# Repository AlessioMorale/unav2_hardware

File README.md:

View this project on [CADLAB.io](https://cadlab.io/project/25058). 

# unav2_hardware
Initial test hardware for the future STM32F4 based uNav motor controller

## baseboard
An initial, unfinished and untested attempt to design a modular design.

## integrated_board
This is the first iteration of the testing hardware. It is being built but is not tested yet.
[more information](integrated_board/README.md)

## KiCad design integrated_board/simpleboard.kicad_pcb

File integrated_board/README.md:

# Integrated Board
This is the first iteration of test hardware for unav2. The board includes a STM32F405 and two DRV8871 drivers.
It supports motor current feedback using two INA186 and global battery current/voltage monitor using an INA219.
Additionally there is an LM75 temperature monitor ic and a fan output.

Link to [Interactive BOM](https://htmlpreview.github.io/?https://raw.githubusercontent.com/AlessioMorale/unav2_hardware/master/integrated_board/bom/ibom.html) (built with the awesome [InteractiveHtmlBom plugin](https://github.com/openscopeproject/InteractiveHtmlBom) )

Note: Encoder, serial and fan connectors are actually JST SH series, not exactly the type shown.

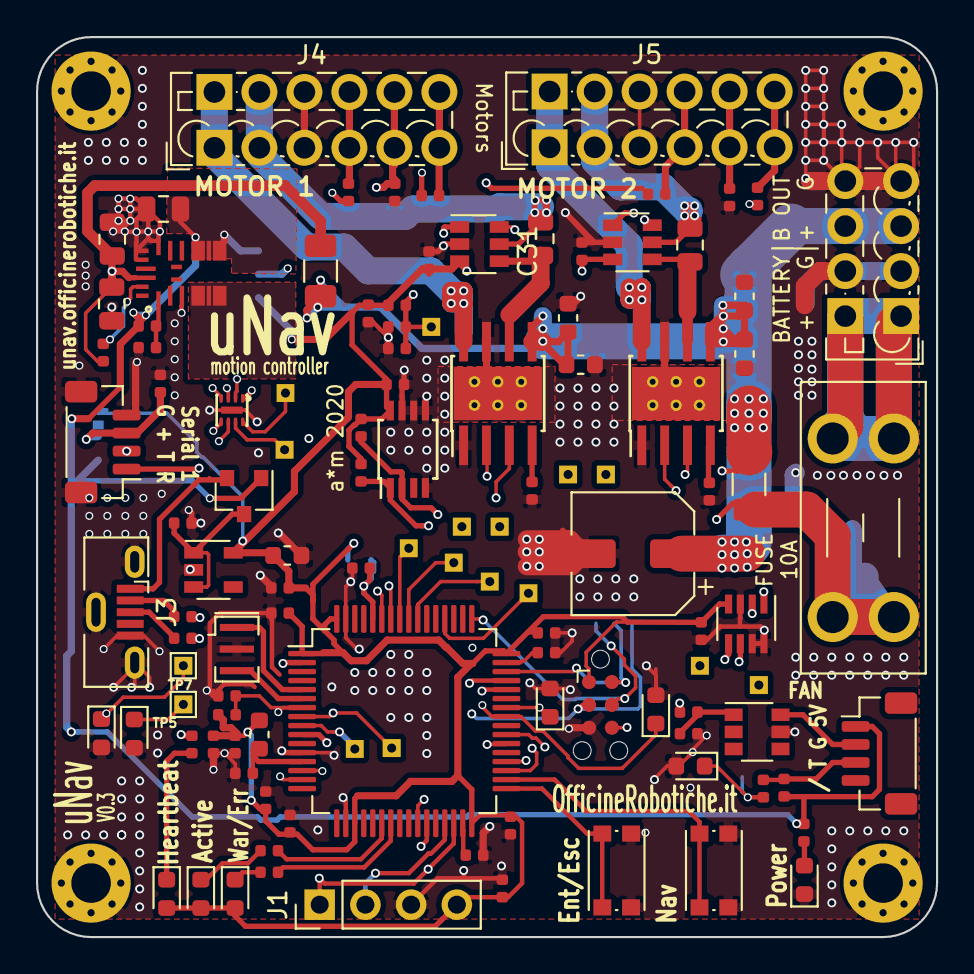
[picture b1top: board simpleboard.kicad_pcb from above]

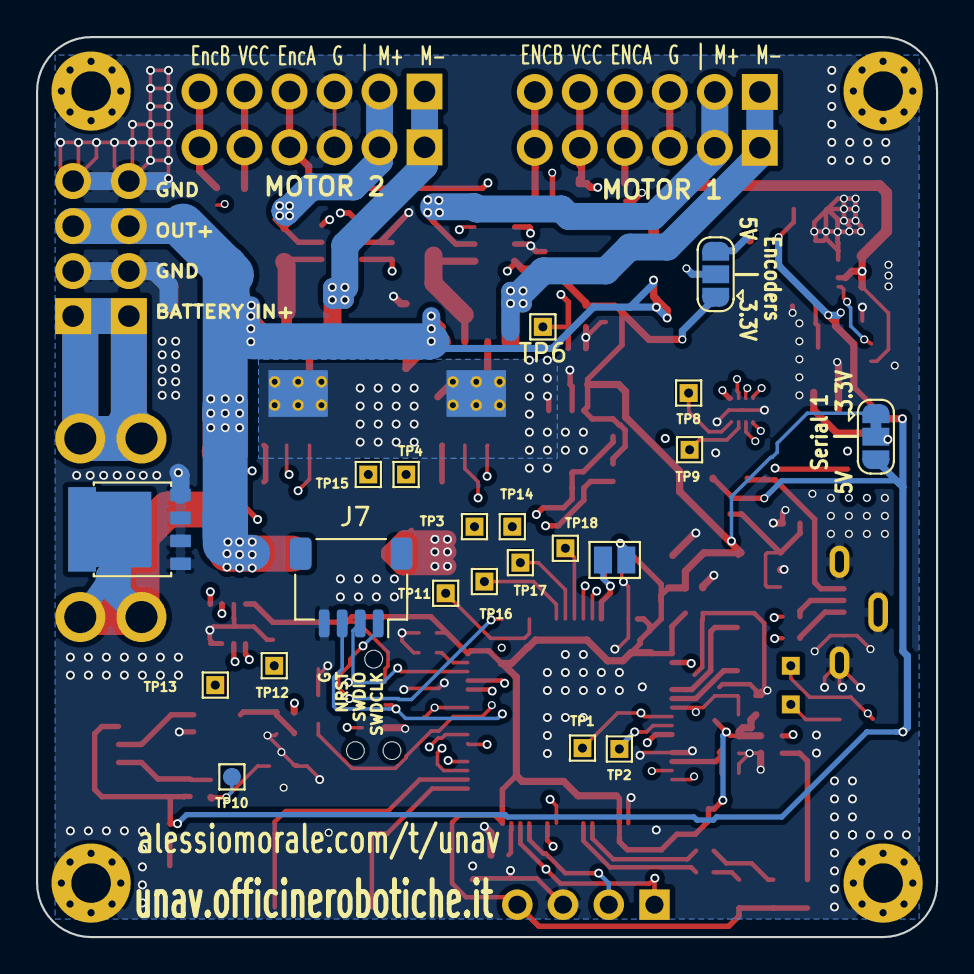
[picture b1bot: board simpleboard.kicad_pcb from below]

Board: 4 copper layers, 50.0 x 50.0 mm, 122 parts (21 on the bottom side), 76 nets.

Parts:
C1: 47uF; CP_Elec_6.3x5.8
C2, C5, C6, C7: 1uF 25V; C_0603_1608Metric
C3, C8, C9, C13, C14, C15, C16, C19, C21, C22, C23, C24, C26, C28, C29, C31, C32: 100nF 16V; C_0402_1005Metric
C4, C11, C12, C25, C27: 1uF 10V; C_0402_1005Metric
C10: 10n; C_0402_1005Metric
C17: 22uF 25V; C_0805_2012Metric
C18: 4.7uf 25V; C_0805_2012Metric
C20: 22uf 6.3V; C_0805_2012Metric
C30: 1uF 6.3V; C_0603_1608Metric
D1: Blue; LED_0603_1608Metric
D2: Yellow; LED_0603_1608Metric
D3: Red; LED_0603_1608Metric
D4: BAT54C; SOT-23
D5: green; LED_0603_1608Metric
D6: STPS3045DJF; LFPAK56
D7, D8, D9, D10: 3.3V; D_0603_1608Metric
D11: D_Zener; D_0603_1608Metric
F1: Fuse_Small; Fuseholder_Blade_Mini_Keystone_3568
F2: Polyfuse_Small; Fuse_1206_3216Metric
H1, H2, H3, H4: MountingHole; MountingHole_2.2mm_M2_Pad_Via
IC1: MPM36xx; QFN-20-MPS-3x5x1.6mm
IC2: IP4251; HUSON8
J1: OLED; PinHeader_1x04_P2.54mm_Vertical
J2: SERIAL1; JST_SH_BM04B-SRSS-TB_1x04-1MP_P1.00mm_Vertical
J3: USB_B_Micro; USB_Micro-B_Molex-105133-0001
J4: Motor1; TerminalBlock_Phoenix_PTSM-0,5-6-2.5-V-THR_1x06_P2.50mm_Ver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
J5: Motor2; TerminalBlock_Phoenix_PTSM-0,5-6-2.5-V-THR_1x06_P2.50mm_Ver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
J6: Battery; TerminalBlock_Phoenix_PTSM-0,5-4-2.5-V-THR_1x04_P2.50mm_Ver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
J7: SWD2; JST_SH_SM04B-SRSS-TB_1x04-1MP_P1.00mm_Horizontal
J8: FAN; JST_SH_BM04B-SRSS-TB_1x04-1MP_P1.00mm_Vertical
JP1: BOOT; SolderJumper-2_P1.3mm_Open_Pad1.0x1.5mm
JP2: S1_VSEL; SolderJumper-3_P1.3mm_Bridged12_RoundedPad1.0x1.5mm
JP3: Jumper_3_Bridged12; SolderJumper-3_P1.3mm_Open_RoundedPad1.0x1.5mm
L1: bead; L_0603_1608Metric
P1: SWD_TC; Tag-Connect_TC2030-IDC-NL_2x03_P1.27mm_Vertical
Q1: FDC6401N; SuperSOT-6
R1, R2, R11, R17, R18, R19, R20, R21, R28: 1k; R_0402_1005Metric
R3, R4: 15k; R_0402_1005Metric
R5, R6: 0.003; R_0805_2012Metric
R7, R8: 47k; R_0402_1005Metric
R9: 220; R_0402_1005Metric
R10: 10k; R_0402_1005Metric
R12: 0.001; R_1206_3216Metric
R13, R22, R23, R24: 330; R_0402_1005Metric
R14, R25: 4.7k; R_0402_1005Metric
R15: 100K; R_0402_1005Metric
R16: 19.1K; R_0402_1005Metric
R26, R27: 22; R_0402_1005Metric
SW1, SW2: KEY_UP; SW_Push_1P1T_NO_CK_KMR2
TP1, TP2, TP3, TP4, TP5, TP6, TP7, TP8, TP9, TP10, TP11, TP12, TP13, TP14, TP15, TP16, TP17, TP18: TestPoint; TestPoint_THTPad_1.0x1.0mm_Drill0.5mm
U1, U6: DRV8871DDA; Texas_HTSOP-8-1EP_3.9x4.9mm_P1.27mm_EP2.95x4.9mm_Mask2.4x3.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
U2: INA219AxDCN; SOT-23-8
U3: LM75B; TSSOP-8_3x3mm_P0.65mm
U4: AP2112K-3.3; SOT-23-5
U5: STM32F405RGTx; LQFP-64_10x10mm_P0.5mm
U7, U8: INA186; SOT-23-6
Y1: 8MHz; Resonator_SMD_muRata_CSTxExxV-3Pin_3.0x1.1mm

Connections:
+3V3: C8.2, C9.2, C13.2, C14.2, C15.1, C16.1, C21.2, C22.2, C23.2, C24.2, C25.2, C27.1, C28.2, C30.1, C32.2, D1.2, D2.2, D3.2, J1.4, JP1.1, JP2.1, JP3.1, L1.1, P1.1, R1.1, R7.1, R14.2, R25.2, U2.4, U3.8, U4.5, U5.1, U5.19, U5.32, U5.48, U5.64, U7.3, U8.3
+5V: C20.1, D4.1, IC1.7, IC1.8, IC1.9, J8.1, JP2.3, JP3.3, R10.2, R15.2, R17.2
/5V_USB: D4.2, J3.1
/ADC_MOT1_CUR: TP1.1, U5.8, U7.6
/ADC_MOT2_CUR: TP2.1, U5.9, U8.6
/ADC_VREF: C4.1, R1.2, R2.1, TP6.1, U5.10, U7.1, U8.1
/BATTERY+: F1.1, J6.1
/BOOT0: JP1.2, R8.1, U5.60
/I2C_SCL: J1.2, R25.1, TP12.1, U2.5, U3.2, U5.29
/I2C_SDA: J1.1, R14.1, TP13.1, U2.6, U3.1, U5.30
/I_KEY0: SW1.1, U5.33
/I_KEY1: SW2.1, U5.34
/NRST: C10.1, J7.3, P1.3, R7.2, U5.7
/O_LED1: R22.1, U5.2
/O_LED2: R23.1, U5.22
/O_LED3: R24.1, U5.23
/O_SPI_CS1: TP11.1, U5.52
/SER1_RX: J2.1, U5.59
/SER1_TX: J2.2, U5.58
/SPI1_MISO: TP17.1, U5.56
/SPI1_MOSI: TP18.1, U5.57
/SPI1_SCK: P1.6, TP16.1, U5.55
/SWCK: J7.1, P1.4, U5.49
/SWDIO: J7.2, P1.2, U5.46
/Sheet5E8E545F/ENC1_A: J4.4, R18.1
/Sheet5E8E545F/ENC1_B: J4.6, R20.1
/Sheet5E8E545F/ENC2_A: J5.4, R19.1
/Sheet5E8E545F/ENC2_B: J5.6, R21.1
/Sheet5E8E545F/ENC_Power: C3.2, C31.1, J4.5, J5.5, JP3.2
/Sheet5E94E0E4/MOT1_A: J4.2, R5.1, U7.5
/Sheet5E94E0E4/MOT1_B: J4.1, U1.8
/Sheet5E94E0E4/MOT2_A: J5.2, R6.1, U8.5
/Sheet5E94E0E4/MOT2_B: J5.1, U6.8
/Sheet5E8941DD/FAN_GND: J8.2, Q1.6
/Sheet5E8941DD/FAN_TACH: J8.3, R10.1, R28.1
/TIM_ENC1_A: D10.1, IC2.1, TP8.1, U5.41
/TIM_ENC1_B: D9.1, IC2.2, TP9.1, U5.42
/TIM_ENC2_A: D8.1, IC2.3, TP7.1, U5.14
/TIM_ENC2_B: D7.1, IC2.4, TP5.1, U5.15
/TIM_FAN_INDEX: D11.1, R28.2, TP10.1, U5.27
/TIM_FAN_PWM: R9.2, U5.26
/TIM_MOT1_A: TP3.1, U1.3, U5.38
/TIM_MOT1_B: TP14.1, U1.2, U5.35
/TIM_MOT2_A: TP4.1, U5.39, U6.3
/TIM_MOT2_B: TP15.1, U5.36, U6.2
/USB_OTG_FS_DM: R27.1, U5.44
/USB_OTG_FS_DP: R26.1, U5.45
/VDDA: C26.1, L1.2, U5.13
/V_BATT_INT: C17.1, C18.1, F2.1, IC1.16, R13.1
GND: C1.2, C2.2, C3.1, C4.2, C5.2, C6.2, C7.2, C8.1, C9.1, C10.2, C11.2, C12.2, C13.1, C14.1, C15.2, C16.2, C17.2, C18.2, C19.2, C20.2, C21.1, C22.1, C23.1, C24.1, C25.1, C26.2, C27.2, C28.1, C29.2, C30.2, C31.2, C32.1, D5.1, D6.1, D6.2, D6.3, D6.4, D7.2, D8.2, D9.2, D10.2, D11.2, H1.1, H2.1, H3.1, H4.1, IC1.3, IC1.12, IC1.13, IC1.14, IC2.9, J1.3, J2.4, J2.MP, J3.5, J3.6, J4.3, J5.3, J6.2, J6.4, J7.4, P1.5, Q1.5, R2.2, R3.2, R4.2, R8.2, R11.1, R16.1, SW1.2, SW2.2, U1.1, U1.7, U1.9, U2.3, U2.7, U2.8, U3.4, U3.5, U3.6, U3.7, U4.2, U5.12, U5.18, U5.63, U6.1, U6.7, U6.9, U7.2, U8.2, Y1.2
unnamed: C11.1, U5.31
unnamed: C12.1, U5.47
unnamed: C19.1, D4.3, U4.1, U4.3
unnamed: C29.1, J2.3, JP2.2
unnamed: D1.1, R22.2
unnamed: D2.1, R23.2
unnamed: D3.1, R24.2
unnamed: D5.2, R17.1
unnamed: D6.5, F1.2, R12.2, U2.1
unnamed: IC1.1, R15.1, R16.2
unnamed: IC1.4, IC1.5, IC1.6
unnamed: IC1.17, R13.2
unnamed: IC2.5, R21.2
unnamed: IC2.6, R19.2
unnamed: IC2.7, R20.2
unnamed: IC2.8, R18.2
unnamed: J3.2, R27.2
unnamed: J3.3, R26.2
unnamed: Q1.1, R9.1, R11.2
unnamed: R3.1, U1.4
unnamed: R4.1, U6.4
unnamed: R5.2, U1.6, U7.4
unnamed: R6.2, U6.6, U8.4
unnamed: U5.5, Y1.1
unnamed: U5.6, Y1.3
VBATT: C1.1, C2.1, C5.1, C6.1, C7.1, F2.2, J6.3, R12.1, U1.5, U2.2, U6.5

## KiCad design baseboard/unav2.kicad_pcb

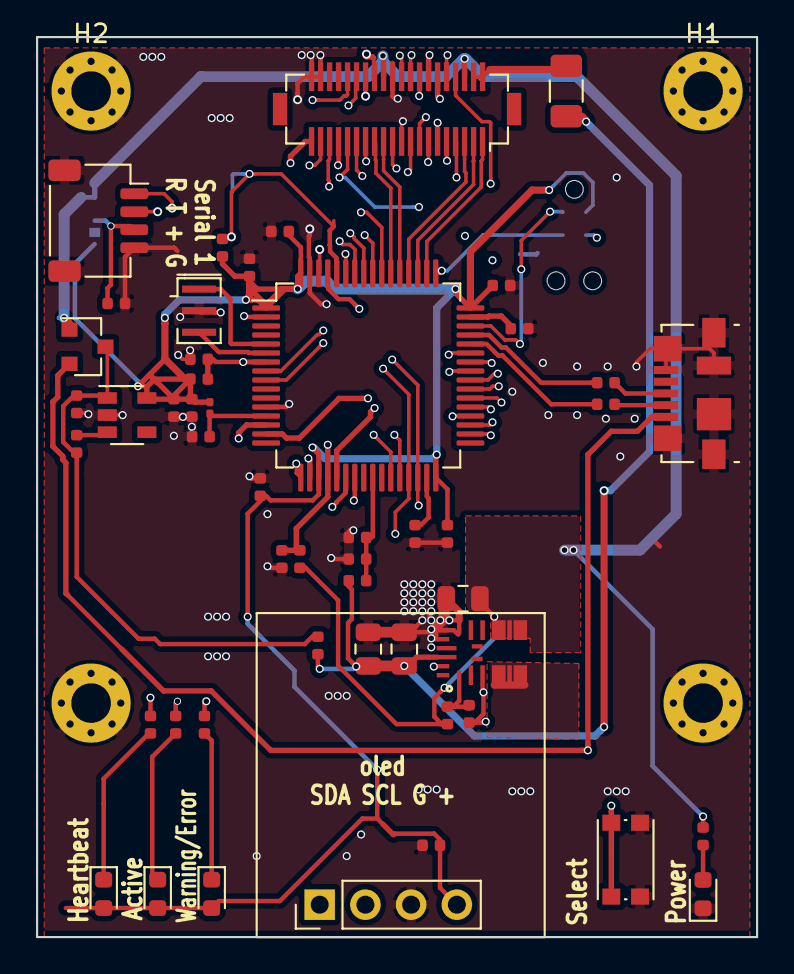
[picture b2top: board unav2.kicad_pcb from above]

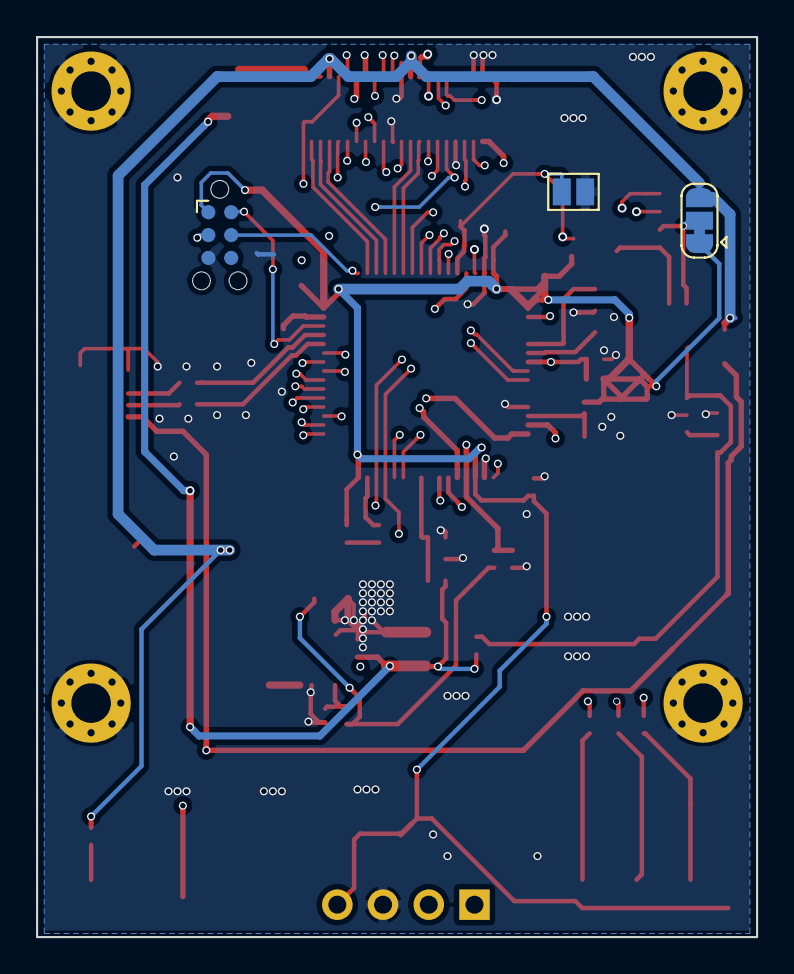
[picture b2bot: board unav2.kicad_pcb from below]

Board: 4 copper layers, 40.0 x 50.0 mm, 57 parts (3 on the bottom side), 65 nets.

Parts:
C3, C7, C13: 1uF; C_0402_1005Metric
C4, C5, C8, C9, C10, C11, C12, C14, C16, C18: 100nF; C_0402_1005Metric
C6, C22: C; C_0402_1005Metric
C15, C19: 4.7uf; C_0805_2012Metric
C17: 22uf; C_0805_2012Metric
C21: 10n; C_0402_1005Metric
D1: White; LED_0603_1608Metric
D2: BAT54C; SOT-23
D3: Blue; LED_0603_1608Metric
D4: Yellow; LED_0603_1608Metric
D5: Red; LED_0603_1608Metric
F1: Polyfuse_Small; Fuse_1206_3216Metric
H1, H2, H3, H4: MountingHole; MountingHole_2.2mm_M2_Pad_Via
IC1: MPM36xx; QFN-20-MPS-3x5x1.6mm
J1: Conn_02x20_Top_Bottom; Hirose_DF12_DF12B-40DS-0.5V(86)
J4: SERIAL1; JST_SH_SM04B-SRSS-TB_1x04-1MP_P1.00mm_Horizontal
J5: OLED; PinHeader_1x04_P2.54mm_Vertical
J6: USB_B_Micro; USB_Micro-B_Molex_47346-0001
JP1: BOOT; SolderJumper-2_P1.3mm_Open_Pad1.0x1.5mm
JP3: S1_VSEL; SolderJumper-3_P1.3mm_Bridged12_RoundedPad1.0x1.5mm
L1: L_Small; L_0201_0603Metric
P1: SWD_TC; Tag-Connect_TC2030-IDC-NL_2x03_P1.27mm_Vertical
R1: 49k; R_0402_1005Metric
R2, R17, R18, R19: 330; R_0402_1005Metric
R3: 10k; R_0402_1005Metric
R4, R5: 10K; R_0402_1005Metric
R6: 22K; R_0402_1005Metric
R7, R14: 47k; R_0402_1005Metric
R10: 22; R_0402_1005Metric
R15, R16: 1k; R_0402_1005Metric
SW1: KEY_UP; SW_Push_1P1T_NO_CK_KMR2
U1: STM32F405RGTx; LQFP-64_10x10mm_P0.5mm
U2: AP2121AK-3.3; SOT-23-5
Y1: 8MHz; Resonator_SMD_muRata_CSTxExxV-3Pin_3.0x1.1mm
e: 22; R_0402_1005Metric

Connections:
+3V3: C4.2, C6.2, C8.2, C9.2, C10.2, C11.2, C12.2, C13.2, D3.2, D4.2, D5.2, J5.4, JP3.1, L1.1, P1.1, R7.1, R14.1, U1.1, U1.19, U1.32, U1.48, U1.64, U2.5
+5V: C17.1, D2.1, IC1.7, IC1.8, IC1.9, J1.23, J1.32, JP3.3, R4.2, R6.2, R16.2
/5V_USB: D2.2, J6.1
/ADC_BATT_VOL: C5.1, R1.1, R15.2, U1.25
/ADC_MOT1_CUR: J1.18, U1.8
/ADC_MOT2_CUR: J1.19, U1.9
/BOOT0: JP1.2, R7.2, U1.60
/I2C_SCL: J1.15, J5.2, U1.29
/I2C_SDA: J1.14, J5.1, U1.30
/I_FAN_INDEX: J1.29, U1.28
/I_FAULT: C18.1, J1.20, R6.1, U1.20
/I_KEY_UP: SW1.1, U1.14
/I_MOT_FAULT: J1.11, U1.34
/NRST: C21.1, P1.3, R14.2, U1.7
/O_LED1: R17.1, U1.2
/O_LED2: R18.1, U1.22
/O_LED3: R19.1, U1.23
/O_MOT_ENABLE: J1.7, U1.37
/O_PWR_MOT_EN: J1.16, U1.43
/O_PWR_SBC_EN: J1.4, U1.40
/O_REG_EN: IC1.17, U1.61
/O_SPI_CS1: J1.3, U1.52
/O_SPI_CS2: J1.2, U1.51
/PA15: J1.1, U1.50
/SER1_RX: J4.1, U1.59
/SER1_TX: J4.2, U1.58
/SER2_RX: J1.13, U1.54
/SER2_TX: J1.12, U1.53
/SPARE_1: J1.33, U1.17
/SPI1_MISO: J1.35, U1.56
/SPI1_MOSI: J1.36, U1.57
/SPI1_SCK: J1.34, U1.55
/SWCK: P1.4, U1.49
/SWDIO: P1.2, U1.46
/TIM_AUX2_PWM: J1.28, U1.62
/TIM_ENC1_A: J1.24, U1.41
/TIM_ENC1_B: J1.25, U1.42
/TIM_ENC2_A: J1.26, U1.21
/TIM_ENC2_B: J1.27, U1.15
/TIM_FAN_PWM: J1.30, U1.27
/TIM_MOT1_A: J1.6, U1.38
/TIM_MOT1_B: J1.9, U1.35
/TIM_MOT2_A: J1.5, U1.39
/TIM_MOT2_B: J1.8, U1.36
/USB_OTG_FS_DM: R10.1, U1.44
/USB_OTG_FS_DP: U1.45, e.1
/V_BATT: C15.1, C19.1, F1.1, IC1.16, R1.2, R2.2
GND: C3.2, C4.1, C5.2, C6.1, C7.2, C8.1, C9.1, C10.1, C11.1, C12.1, C13.1, C14.2, C15.2, C16.2, C17.2, C18.2, C19.2, C21.2, C22.2, D1.1, H1.1, H2.1, H3.1, H4.1, IC1.3, IC1.12, IC1.13, IC1.14, J1.10, J1.17, J1.31, J1.39, J1.40, J4.4, J4.MP, J5.3, J6.5, J6.6, JP1.1, P1.5, R5.1, R15.1, SW1.2, U1.12, U1.18, U1.63, U2.2, Y1.2
unnamed: C3.1, U1.31
unnamed: C7.1, U1.47
unnamed: C14.1, L1.2, U1.13
unnamed: C16.1, D2.3, R2.1, R3.1, U2.1
unnamed: C22.1, J4.3, JP3.2
unnamed: D1.2, R16.1
unnamed: D3.1, R17.2
unnamed: D4.1, R18.2
unnamed: D5.1, R19.2
unnamed: F1.2, J1.21, J1.22
unnamed: IC1.1, R4.1, R5.2
unnamed: IC1.4, IC1.5, IC1.6
unnamed: J6.2, R10.2
unnamed: J6.3, e.2
unnamed: R3.2, U2.3
unnamed: U1.5, Y1.1
unnamed: U1.6, Y1.3

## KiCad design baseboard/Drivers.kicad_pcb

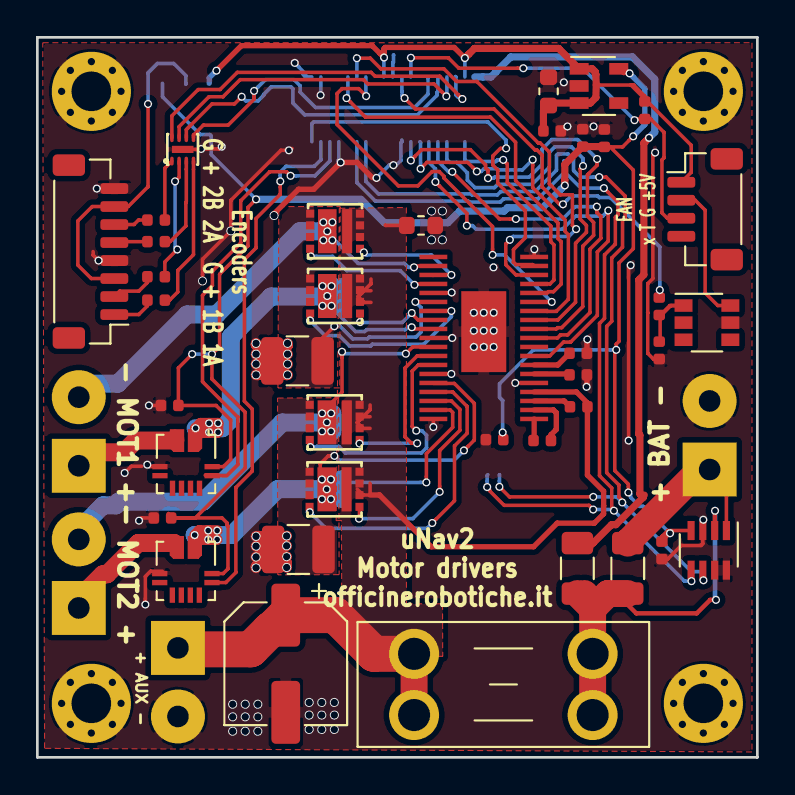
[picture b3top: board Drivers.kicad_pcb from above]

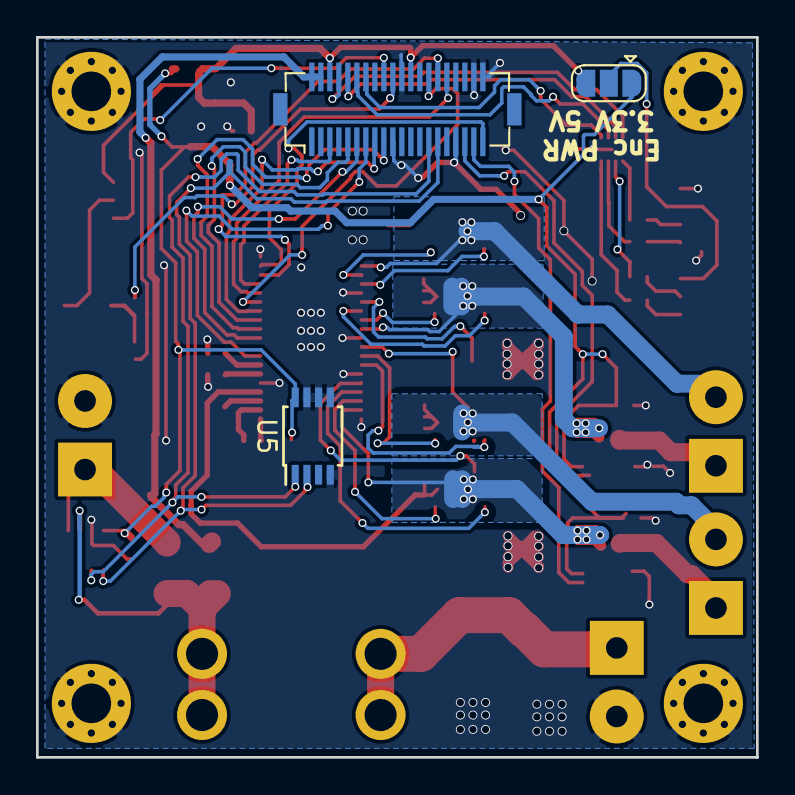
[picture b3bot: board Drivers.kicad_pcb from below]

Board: 2 copper layers, 40.0 x 40.0 mm, 50 parts (3 on the bottom side), 59 nets.

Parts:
C1, C7: 1uF; C_0603_1608Metric
C2, C3, C4, C14: 100n; C_0402_1005Metric
C5: 1uF; C_0402_1005Metric
C6: 47uF; CP_Elec_6.3x5.8
C8, C9: 100nF; C_0402_1005Metric
C10, C11: 0.1uF 20V X7R; C_0402_1005Metric
C12, C13: 1uF 16V X7R; C_0402_1005Metric
F1: Fuse_Small; Fuseholder_Blade_Mini_Keystone_3568
F2: Polyfuse_Small; Fuse_1206_3216Metric
H1, H2, H3, H4: MountingHole; MountingHole_2.2mm_M2_Pad_Via
IC1: IP4251; HUSON8
IC2: DRV8704; HTSSOP-38
J1: Conn_02x20_Top_Bottom; Hirose_DF12_DF12B(3.5)-40DP-0.5V(86)
J2: M1; SolderWirePad_1x02_P3.81mm_Drill1.2mm
J3: M2; SolderWirePad_1x02_P3.81mm_Drill1.2mm
J4: Battery; SolderWirePad_1x02_P3.81mm_Drill1.2mm
J5: SBC; SolderWirePad_1x02_P3.81mm_Drill1.2mm
J6: Enc; JST_SH_BM08B-SRSS-TB_1x08-1MP_P1.00mm_Vertical
J7: FAN; JST_SH_BM04B-SRSS-TB_1x04-1MP_P1.00mm_Vertical
JP1: Jumper_3_Bridged12; SolderJumper-3_P1.3mm_Open_RoundedPad1.0x1.5mm
Q1, Q2, Q3, Q4: SiZ340DT; PowerPair-3x3
Q5: Q_DUAL_NMOS_G1S2G2D2S1D1; SuperSOT-6
R1: 0.01; R_1206_3216Metric
R2, R3, R4, R5: 1K; R_0402_1005Metric
R6, R7: R_Small; R_1210_3225Metric
R8: 220; R_0402_1005Metric
R9: 10k; R_0402_1005Metric
R10: 1k; R_0402_1005Metric
U1: INA219AxDCN; SOT-23-8
U2: AP2112K-3.3; SOT-23-5
U3, U4: ACS711xEXLT-31AB; Allegro_QFN-12-10-1EP_3x3mm_P0.5mm
U5: LM75B; TSSOP-8_3x3mm_P0.65mm

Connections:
+3V3: C3.1, C4.1, C5.1, C8.1, C9.1, C14.1, JP1.1, U1.4, U2.5, U3.10, U4.10, U5.8
+5V: C1.1, C2.1, J1.23, J1.32, J7.1, JP1.3, R9.2, U2.1, U2.3
/ADC_MOT1_CUR: J1.18, U3.9
/ADC_MOT2_CUR: J1.19, U4.9
/BATTERY+: J4.1, R1.2, U1.1
/I2C_SCL: J1.15, U1.5, U5.2
/I2C_SDA: J1.14, U1.6, U5.1
/I_FAN_INDEX: J1.29, J7.3, R9.1
/I_FAULT: IC2.18, J1.20
/O_MOT_ENABLE: IC2.8, J1.7
/O_SPI_CS1: IC2.16, J1.3
/SPI1_MISO: IC2.17, J1.35
/SPI1_MOSI: IC2.15, J1.36
/SPI1_SCK: IC2.14, J1.34
/Sheet5E8E545F/ENC1_A: J6.1, R2.1
/Sheet5E8E545F/ENC1_B: J6.2, R4.1
/Sheet5E8E545F/ENC2_A: J6.5, R3.1
/Sheet5E8E545F/ENC2_B: J6.6, R5.1
/Sheet5E8E545F/ENC_Power: J6.3, J6.7, JP1.2
/Sheet5E94E0E4/MOT1_A: J2.1, U3.2
/Sheet5E94E0E4/MOT1_B: IC2.21, J2.2, Q3.S1D2
/Sheet5E94E0E4/MOT2_A: J3.1, U4.2
/Sheet5E94E0E4/MOT2_B: IC2.30, J3.2, Q4.S1D2
/Sheet5E8941DD/FAN_GND: J7.2, Q5.6
/TIM_ENC1_A: IC1.1, J1.24
/TIM_ENC1_B: IC1.2, J1.25
/TIM_ENC2_A: IC1.3, J1.26
/TIM_ENC2_B: IC1.4, J1.27
/TIM_FAN_PWM: J1.30, R8.2
/TIM_MOT1_A: IC2.10, J1.6
/TIM_MOT1_B: IC2.11, J1.9
/TIM_MOT2_A: IC2.12, J1.5
/TIM_MOT2_B: IC2.13, J1.8
/V_BATT: C6.1, C7.1, C12.2, F1.2, IC2.4, J5.1, Q1.D1, Q2.D1, Q3.D1, Q4.D1
/V_BATT_INT: F2.1, J1.21, J1.22
GND: C1.2, C2.2, C3.2, C4.2, C5.2, C6.2, C7.2, C8.2, C9.2, C10.2, C13.2, C14.2, H1.1, H2.1, H3.1, H4.1, IC1.9, IC2.5, IC2.19, IC2.24, IC2.29, IC2.33, IC2.38, IC2.39, J1.10, J1.17, J1.31, J1.39, J1.40, J4.2, J5.2, J6.4, J6.8, Q5.5, R6.2, R7.2, R10.1, U1.3, U1.7, U1.8, U2.2, U3.3, U4.3, U5.4, U5.5, U5.6, U5.7
unnamed: C10.1, IC2.7
unnamed: C11.1, IC2.1
unnamed: C11.2, IC2.2
unnamed: C12.1, IC2.3
unnamed: C13.1, IC2.6
unnamed: F1.1, F2.2, R1.1, U1.2
unnamed: IC1.5, R2.2
unnamed: IC1.6, R3.2
unnamed: IC1.7, R4.2
unnamed: IC1.8, R5.2
unnamed: IC2.22, Q3.G1
unnamed: IC2.23, Q3.G2
unnamed: IC2.25, Q1.S2, Q3.S2, R6.1
unnamed: IC2.26, Q1.G2
unnamed: IC2.27, Q1.G1
unnamed: IC2.28, Q1.S1D2, U3.1
unnamed: IC2.31, Q4.G1
unnamed: IC2.32, Q4.G2
unnamed: IC2.34, Q2.S2, Q4.S2, R7.1
unnamed: IC2.35, Q2.G2
unnamed: IC2.36, Q2.G1
unnamed: IC2.37, Q2.S1D2, U4.1
unnamed: Q5.1, R8.1, R10.2

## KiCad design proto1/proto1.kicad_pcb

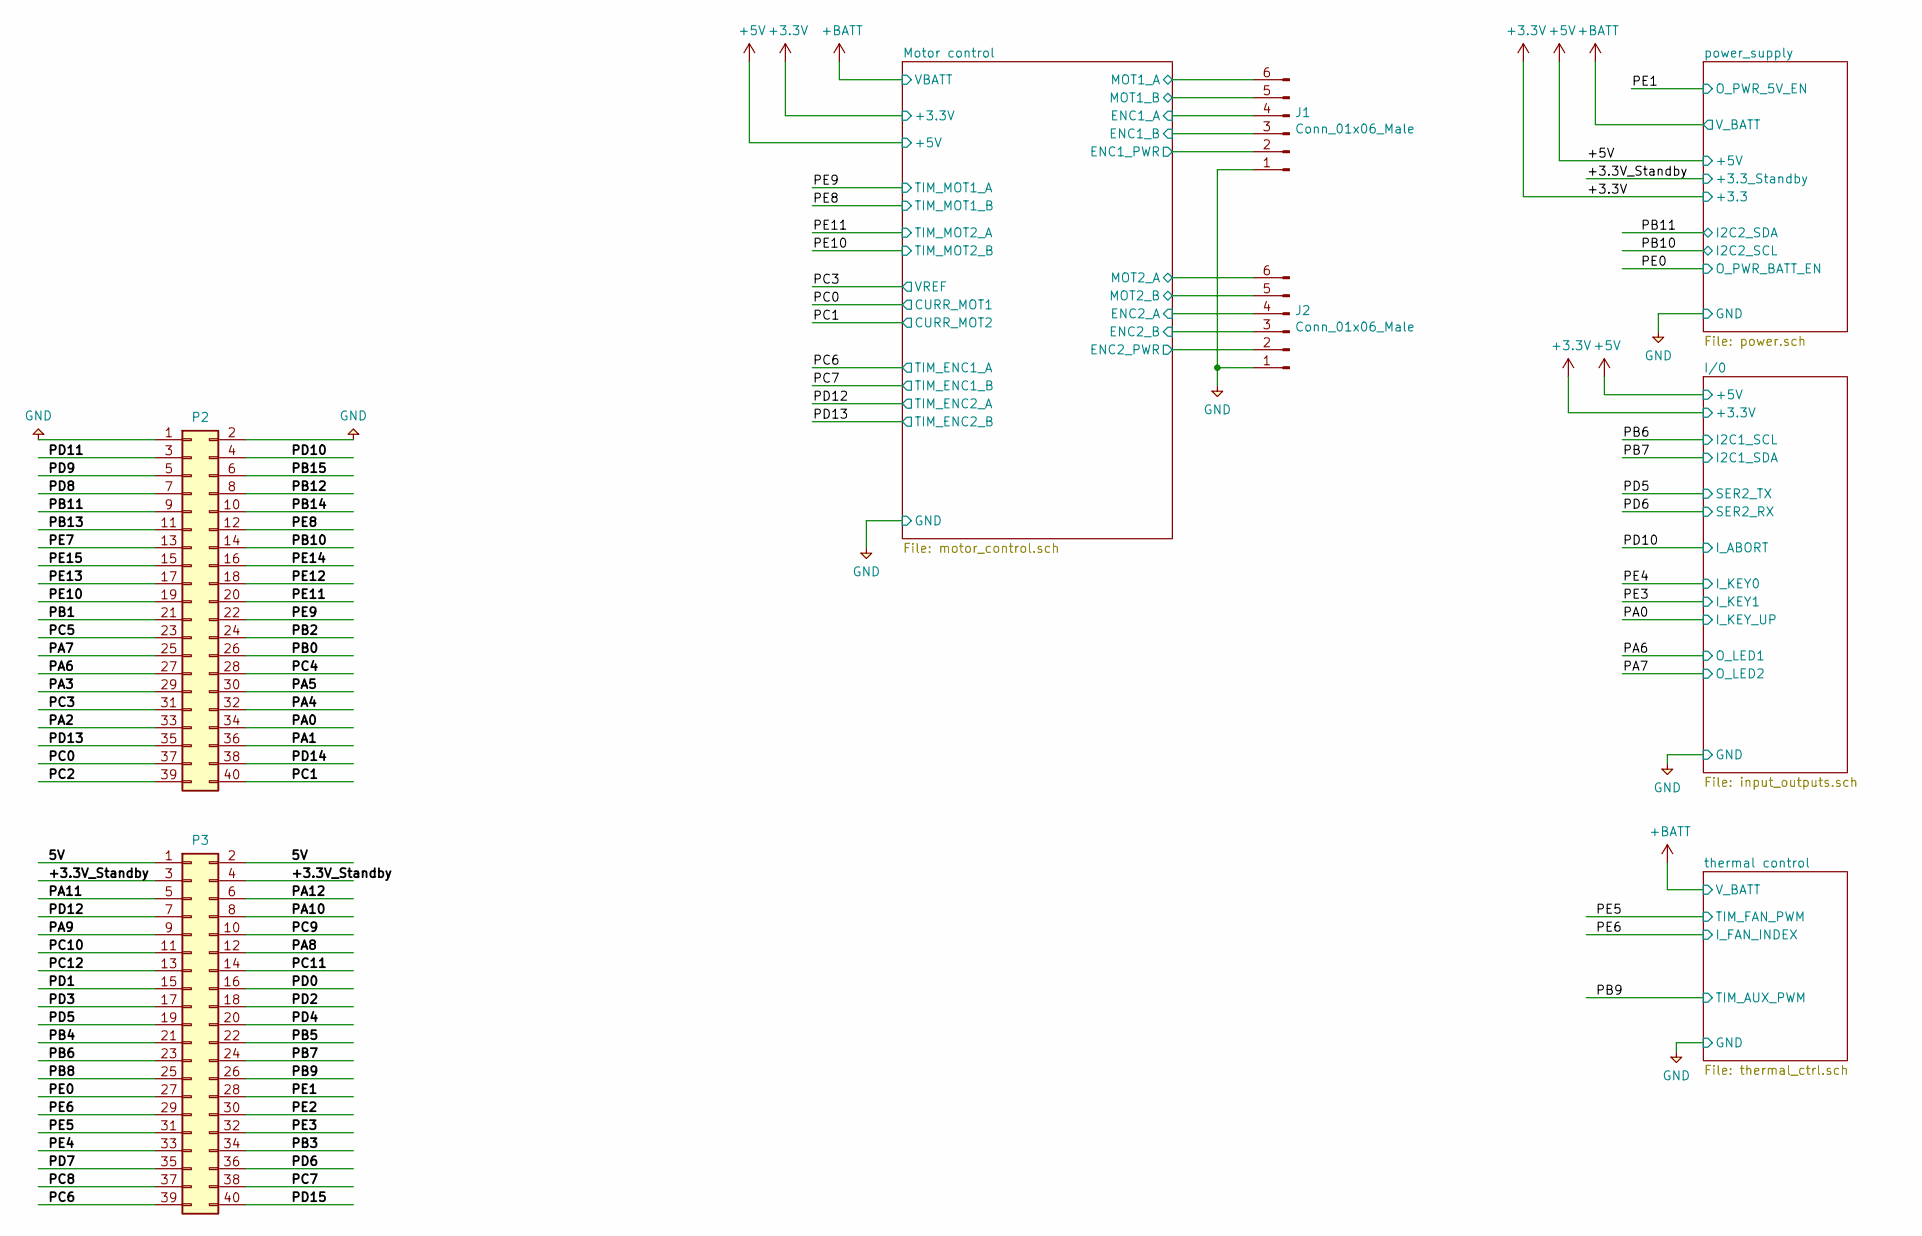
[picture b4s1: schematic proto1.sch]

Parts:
J1, J2: Conn_01x06_Male; PinSocket_1x06_P2.54mm_Vertical
P2, P3: Conn_02x20_Odd_Even; PinHeader_2x20_P2.54mm_Vertical

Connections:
/5V: P3.1, P3.2
/+3.3V_Standby: P3.3, P3.4; also elsewhere on the board
/Motor control/ENC1_A: J1.4; also elsewhere on the board
/Motor control/ENC1_B: J1.3; also elsewhere on the board
/Motor control/ENC1_PWR: J1.2, J2.2; also elsewhere on the board
/Motor control/ENC2_A: J2.4; also elsewhere on the board
/Motor control/ENC2_B: J2.3; also elsewhere on the board
/Motor control/MOT1_A: J1.6; also elsewhere on the board
/Motor control/MOT1_B: J1.5; also elsewhere on the board
/Motor control/MOT2_A: J2.6; also elsewhere on the board
/Motor control/MOT2_B: J2.5; also elsewhere on the board
/PA0: P2.34; also elsewhere on the board
/PA1: P2.36
/PA2: P2.33
/PA3: P2.29
/PA4: P2.32
/PA5: P2.30
/PA6: P2.27; also elsewhere on the board
/PA7: P2.25; also elsewhere on the board
/PA8: P3.12
/PA9: P3.9
/PA10: P3.8
/PA11: P3.5
/PA12: P3.6
/PB0: P2.26
/PB1: P2.21
/PB2: P2.24
/PB3: P3.34
/PB4: P3.21
/PB5: P3.22
/PB6: P3.23; also elsewhere on the board
/PB7: P3.24; also elsewhere on the board
/PB8: P3.25
/PB9: P3.26; also elsewhere on the board
/PB10: P2.14; also elsewhere on the board
/PB11: P2.9; also elsewhere on the board
/PB12: P2.8
/PB13: P2.11
/PB14: P2.10
/PB15: P2.6
/PC0: P2.37; also elsewhere on the board
/PC1: P2.40; also elsewhere on the board
/PC2: P2.39
/PC3: P2.31; also elsewhere on the board
/PC4: P2.28
/PC5: P2.23
/PC6: P3.39; also elsewhere on the board
/PC7: P3.38; also elsewhere on the board
/PC8: P3.37
/PC9: P3.10
/PC10: P3.11
/PC11: P3.14
/PC12: P3.13
/PD0: P3.16
/PD1: P3.15
/PD2: P3.18
/PD3: P3.17
/PD4: P3.20
/PD5: P3.19; also elsewhere on the board
/PD6: P3.36; also elsewhere on the board
/PD7: P3.35
/PD8: P2.7
/PD9: P2.5
/PD10: P2.4; also elsewhere on the board
/PD11: P2.3
/PD12: P3.7; also elsewhere on the board
/PD13: P2.35; also elsewhere on the board
/PD14: P2.38
/PD15: P3.40
/PE0: P3.27; also elsewhere on the board
/PE1: P3.28; also elsewhere on the board
/PE2: P3.30
/PE3: P3.32; also elsewhere on the board
/PE4: P3.33; also elsewhere on the board
/PE5: P3.31; also elsewhere on the board
/PE6: P3.29; also elsewhere on the board
/PE7: P2.13
/PE8: P2.12; also elsewhere on the board
/PE9: P2.22; also elsewhere on the board
/PE10: P2.19; also elsewhere on the board
/PE11: P2.20; also elsewhere on the board
/PE12: P2.18
/PE13: P2.17
/PE14: P2.16
/PE15: P2.15
GND: J1.1, J2.1, P2.1, P2.2; also elsewhere on the board

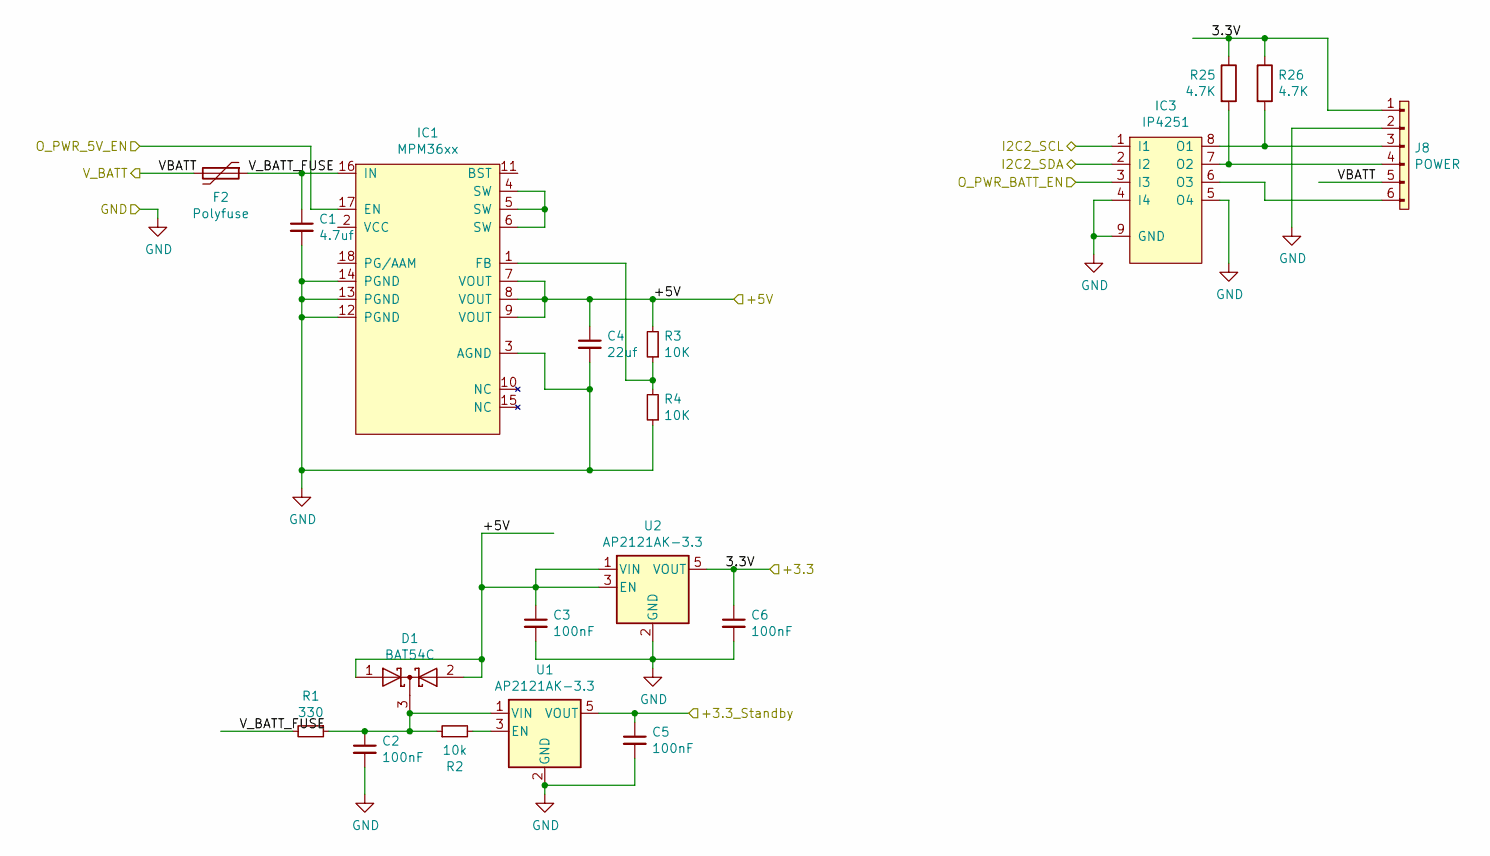
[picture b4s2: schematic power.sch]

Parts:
C1: 4.7uf; C_0805_2012Metric
C2, C3, C5, C6: 100nF; C_0402_1005Metric
C4: 22uf; C_0805_2012Metric
D1: BAT54C; SOT-23
F2: Polyfuse; R_1206_3216Metric
IC1: MPM36xx; QFN-20-MPS-3x5x1.6mm; Digikey 1589-1247-1-ND
IC3: IP4251; HUSON8; Digikey 1727-5678-1-ND
J8: POWER; PinHeader_1x06_P2.54mm_Vertical
R1: 330; R_0402_1005Metric
R2: 10k; R_0402_1005Metric
R3, R4: 10K; R_0402_1005Metric
R25, R26: 4.7K; R_0402_1005Metric
U1, U2: AP2121AK-3.3; SOT-23-5

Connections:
+3V3: C6.1, J8.1, R25.1, R26.1, U2.5 (VOUT); also elsewhere on the board
+5V: C3.1, C4.1, D1.1 (A), D1.2 (A), IC1.7 (VOUT), IC1.8 (VOUT), IC1.9 (VOUT), R3.2, U2.1 (VIN), U2.3 (EN); also elsewhere on the board
+BATT: F2.2, J8.5; also elsewhere on the board
/+3.3V_Standby: C5.1, U1.5 (VOUT); also elsewhere on the board
/PB10: IC3.1 (I1); also elsewhere on the board
/PB11: IC3.2 (I2); also elsewhere on the board
/PE0: IC3.3 (I3); also elsewhere on the board
/PE1: IC1.17 (EN); also elsewhere on the board
/power_supply/V_BATT_FUSE: C1.1, F2.1, IC1.16 (IN), R1.2
GND: C1.2, C2.2, C3.2, C4.2, C5.2, C6.2, IC1.3 (AGND), IC1.12 (PGND), IC1.13 (PGND), IC1.14 (PGND), IC3.4 (I4), IC3.5 (O4), IC3.9 (GND), J8.2, R4.1, U1.2 (GND), U2.2 (GND); also elsewhere on the board
unnamed: C2.1, D1.3 (K), R1.1, R2.1, U1.1 (VIN)
unnamed: IC1.1 (FB), R3.1, R4.2
unnamed: IC1.4 (SW), IC1.5 (SW), IC1.6 (SW)
unnamed: IC3.6 (O3), J8.6
unnamed: IC3.7 (O2), J8.4, R25.2
unnamed: IC3.8 (O1), J8.3, R26.2
unnamed: R2.2, U1.3 (EN)

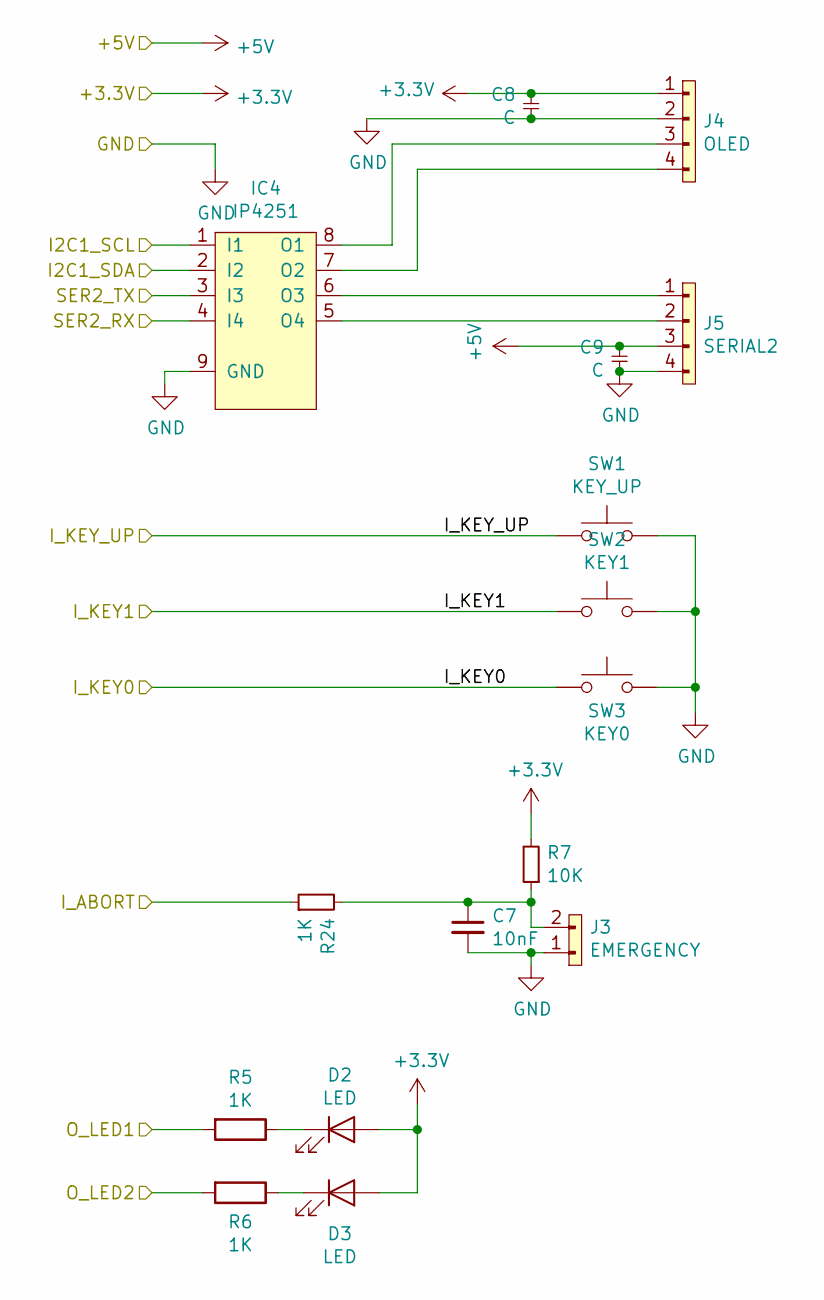
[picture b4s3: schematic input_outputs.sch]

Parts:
C7: 10nF; C_0402_1005Metric
C8, C9: C; C_0402_1005Metric
D2, D3: LED; LED_0603_1608Metric
IC4: IP4251; HUSON8; Digikey 1727-5678-1-ND
J3: EMERGENCY; PinHeader_1x02_P2.54mm_Vertical
J4: OLED; PinHeader_1x04_P2.54mm_Horizontal
J5: SERIAL2; PinHeader_1x04_P2.54mm_Vertical
R5, R6, R24: 1K; R_0402_1005Metric
R7: 10K; R_0402_1005Metric
SW1: KEY_UP; SW_SPST_B3U-1000P
SW2: KEY1; SW_SPST_B3U-1000P
SW3: KEY0; SW_SPST_B3U-1000P

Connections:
+3V3: C8.1, D2.2 (A), D3.2 (A), J4.1, R7.2; also elsewhere on the board
+5V: C9.1, J5.3; also elsewhere on the board
/PA0: SW1.1; also elsewhere on the board
/PA6: R5.2; also elsewhere on the board
/PA7: R6.2; also elsewhere on the board
/PB6: IC4.1 (I1); also elsewhere on the board
/PB7: IC4.2 (I2); also elsewhere on the board
/PD5: IC4.3 (I3); also elsewhere on the board
/PD6: IC4.4 (I4); also elsewhere on the board
/PD10: R24.1; also elsewhere on the board
/PE3: SW2.1; also elsewhere on the board
/PE4: SW3.1; also elsewhere on the board
GND: C7.2, C8.2, C9.2, IC4.9 (GND), J3.1, J4.2, J5.4, SW1.2, SW2.2, SW3.2; also elsewhere on the board
unnamed: C7.1, J3.2, R7.1, R24.2
unnamed: D2.1 (K), R5.1
unnamed: D3.1 (K), R6.1
unnamed: IC4.5 (O4), J5.2
unnamed: IC4.6 (O3), J5.1
unnamed: IC4.7 (O2), J4.4
unnamed: IC4.8 (O1), J4.3

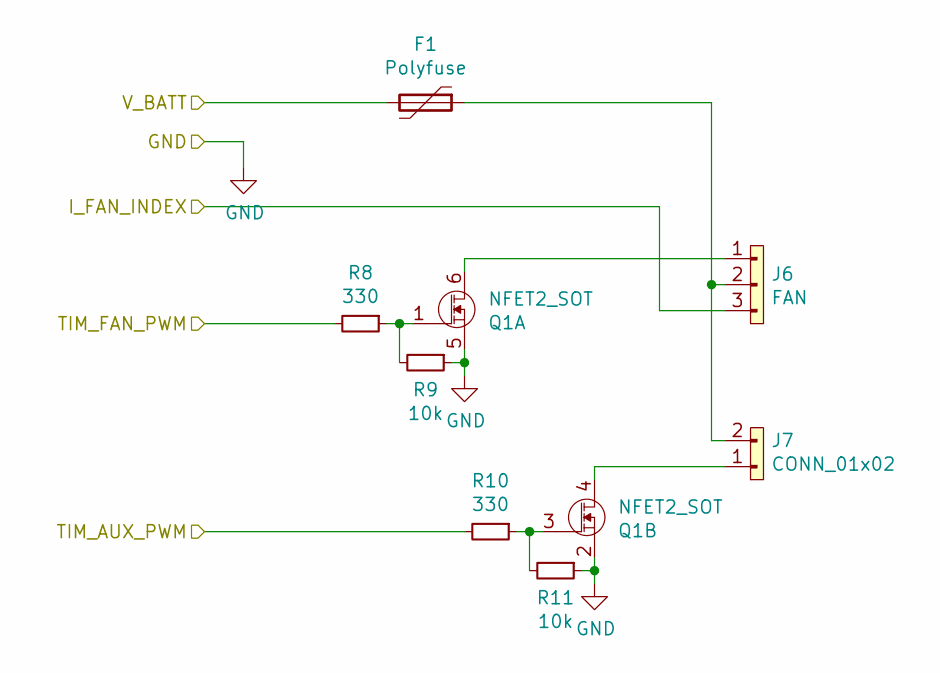
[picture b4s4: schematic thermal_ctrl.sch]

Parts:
F1: Polyfuse; R_1206_3216Metric
J6: FAN; PinHeader_1x03_P2.54mm_Vertical
J7: CONN_01x02; PinHeader_1x02_P2.54mm_Vertical
Q1: NFET2_SOT; SOT-23-6
R8, R10: 330; R_0402_1005Metric
R9, R11: 10k; R_0402_1005Metric

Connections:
+BATT: F1.2; also elsewhere on the board
/PB9: R10.2; also elsewhere on the board
/PE5: R8.2; also elsewhere on the board
/PE6: J6.3; also elsewhere on the board
GND: Q1.2 (S), Q1.5 (S), R9.1, R11.1; also elsewhere on the board
unnamed: F1.1, J6.2, J7.2
unnamed: J6.1, Q1.6 (D)
unnamed: J7.1, Q1.4 (D)
unnamed: Q1.1 (G), R8.1, R9.2
unnamed: Q1.3 (G), R10.1, R11.2
